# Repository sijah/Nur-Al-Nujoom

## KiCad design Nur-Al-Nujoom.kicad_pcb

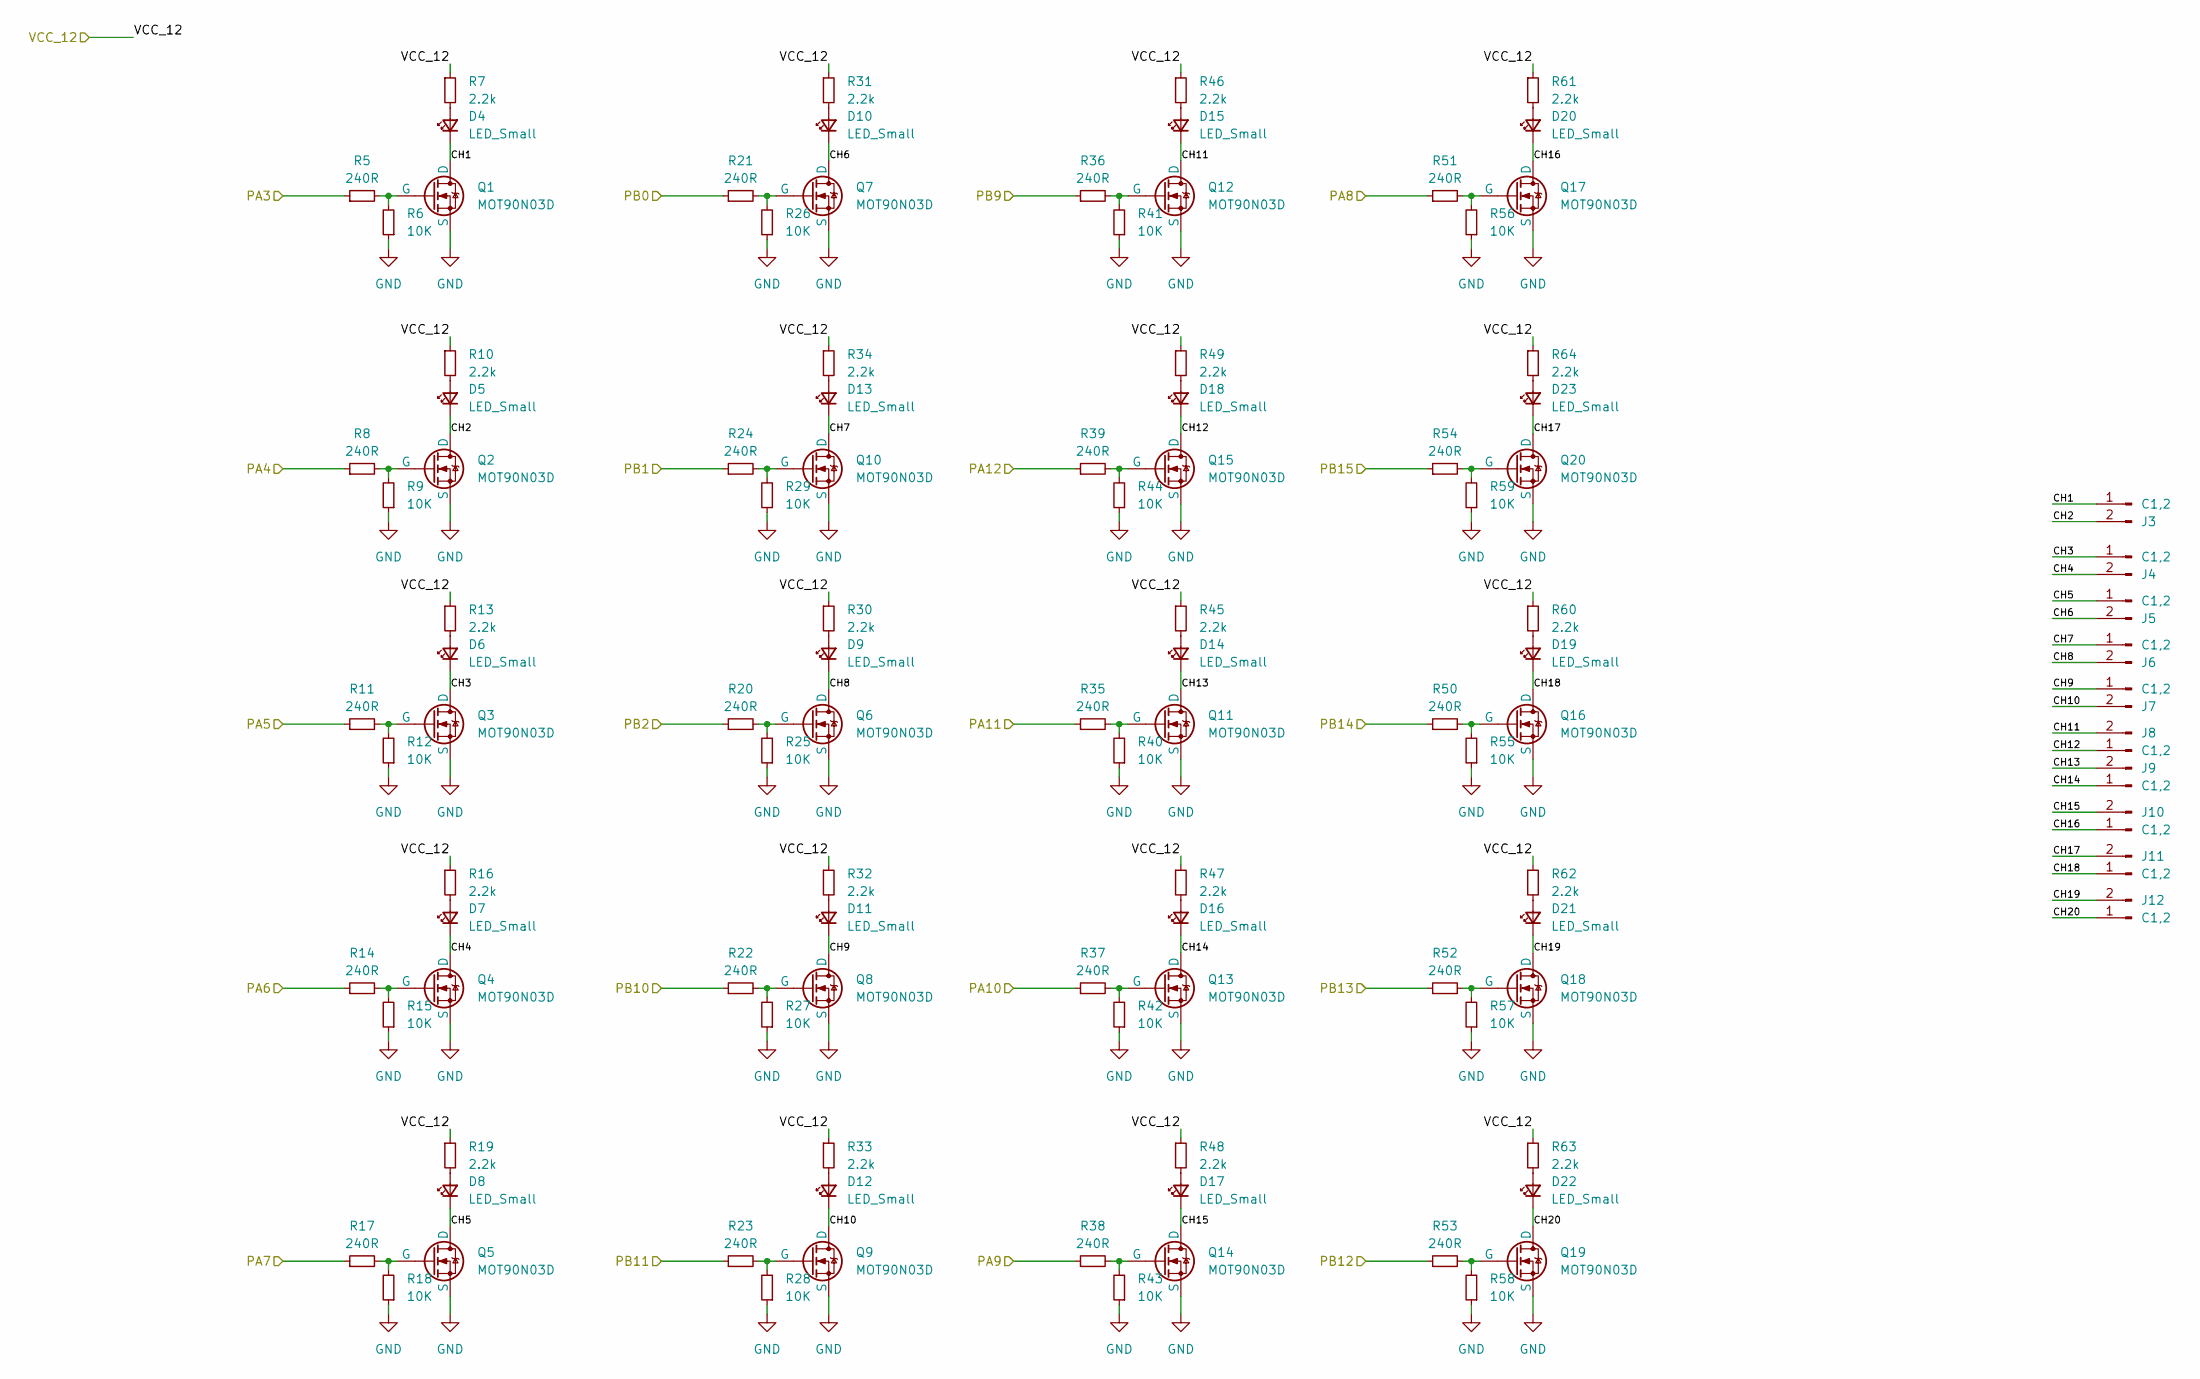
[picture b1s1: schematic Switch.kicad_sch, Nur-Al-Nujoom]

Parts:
D4, D5, D6, D7, D8, D9, D10, D11, D12, D13, D14, D15, D16, D17, D18, D19, D20, D21, D22, D23: LED_Small; LED_0603_1608Metric
J3, J4, J5, J6, J7, J8, J9, J10, J11, J12: C1,2; TerminalBlock_Phoenix_MKDS-3-2-5.08_1x02_P5.08mm_Horizontal
Q1, Q2, Q3, Q4, Q5, Q6, Q7, Q8, Q9, Q10, Q11, Q12, Q13, Q14, Q15, Q16, Q17, Q18, Q19, Q20: MOT90N03D; TO-252-2; mpn MOT90N03D
R5, R8, R11, R14, R17, R20, R21, R22, R23, R24, R35, R36, R37, R38, R39, R50, R51, R52, R53, R54: 240R; R_0603_1608Metric
R6, R9, R12, R15, R18, R25, R26, R27, R28, R29, R40, R41, R42, R43, R44, R55, R56, R57, R58, R59: 10K; R_0603_1608Metric
R7, R10, R13, R16, R19, R30, R31, R32, R33, R34, R45, R46, R47, R48, R49, R60, R61, R62, R63, R64: 2.2k; R_0603_1608Metric

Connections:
/12: R7.1, R10.1, R13.1, R16.1, R19.1, R30.1, R31.1, R32.1, R33.1, R34.1, R45.1, R46.1, R47.1, R48.1, R49.1, R60.1, R61.1, R62.1, R63.1, R64.1; also elsewhere on the board
/MCU/PA3: R5.1; also elsewhere on the board
/MCU/PA4: R8.1; also elsewhere on the board
/MCU/PA5: R11.1; also elsewhere on the board
/MCU/PA6: R14.1; also elsewhere on the board
/MCU/PA7: R17.1; also elsewhere on the board
/MCU/PA8: R51.1; also elsewhere on the board
/MCU/PA9: R38.1; also elsewhere on the board
/MCU/PA10: R37.1; also elsewhere on the board
/MCU/PA11: R35.1; also elsewhere on the board
/MCU/PA12: R39.1; also elsewhere on the board
/MCU/PB0: R21.1; also elsewhere on the board
/MCU/PB1: R24.1; also elsewhere on the board
/MCU/PB2: R20.1; also elsewhere on the board
/MCU/PB9: R36.1; also elsewhere on the board
/MCU/PB10: R22.1; also elsewhere on the board
/MCU/PB11: R23.1; also elsewhere on the board
/MCU/PB12: R53.1; also elsewhere on the board
/MCU/PB13: R52.1; also elsewhere on the board
/MCU/PB14: R50.1; also elsewhere on the board
/MCU/PB15: R54.1; also elsewhere on the board
/Switch/CH1: D4.1 (K), J3.1, Q1.2 (D)
/Switch/CH2: D5.1 (K), J3.2, Q2.2 (D)
/Switch/CH3: D6.1 (K), J4.1, Q3.2 (D)
/Switch/CH4: D7.1 (K), J4.2, Q4.2 (D)
/Switch/CH5: D8.1 (K), J5.1, Q5.2 (D)
/Switch/CH6: D10.1 (K), J5.2, Q7.2 (D)
/Switch/CH7: D13.1 (K), J6.1, Q10.2 (D)
/Switch/CH8: D9.1 (K), J6.2, Q6.2 (D)
/Switch/CH9: D11.1 (K), J7.1, Q8.2 (D)
/Switch/CH10: D12.1 (K), J7.2, Q9.2 (D)
/Switch/CH11: D15.1 (K), J8.2, Q12.2 (D)
/Switch/CH12: D18.1 (K), J8.1, Q15.2 (D)
/Switch/CH13: D14.1 (K), J9.2, Q11.2 (D)
/Switch/CH14: D16.1 (K), J9.1, Q13.2 (D)
/Switch/CH15: D17.1 (K), J10.2, Q14.2 (D)
/Switch/CH16: D20.1 (K), J10.1, Q17.2 (D)
/Switch/CH17: D23.1 (K), J11.2, Q20.2 (D)
/Switch/CH18: D19.1 (K), J11.1, Q16.2 (D)
/Switch/CH19: D21.1 (K), J12.2, Q18.2 (D)
/Switch/CH20: D22.1 (K), J12.1, Q19.2 (D)
GND: Q1.3 (S), Q2.3 (S), Q3.3 (S), Q4.3 (S), Q5.3 (S), Q6.3 (S), Q7.3 (S), Q8.3 (S), Q9.3 (S), Q10.3 (S), Q11.3 (S), Q12.3 (S), Q13.3 (S), Q14.3 (S), Q15.3 (S), Q16.3 (S), Q17.3 (S), Q18.3 (S), Q19.3 (S), Q20.3 (S), R6.1, R9.1, R12.1, R15.1, R18.1, R25.1, R26.1, R27.1, R28.1, R29.1, R40.1, R41.1, R42.1, R43.1, R44.1, R55.1, R56.1, R57.1, R58.1, R59.1; also elsewhere on the board
unnamed: D4.2 (A), R7.2
unnamed: D5.2 (A), R10.2
unnamed: D6.2 (A), R13.2
unnamed: D7.2 (A), R16.2
unnamed: D8.2 (A), R19.2
unnamed: D9.2 (A), R30.2
unnamed: D10.2 (A), R31.2
unnamed: D11.2 (A), R32.2
unnamed: D12.2 (A), R33.2
unnamed: D13.2 (A), R34.2
unnamed: D14.2 (A), R45.2
unnamed: D15.2 (A), R46.2
unnamed: D16.2 (A), R47.2
unnamed: D17.2 (A), R48.2
unnamed: D18.2 (A), R49.2
unnamed: D19.2 (A), R60.2
unnamed: D20.2 (A), R61.2
unnamed: D21.2 (A), R62.2
unnamed: D22.2 (A), R63.2
unnamed: D23.2 (A), R64.2
unnamed: Q1.1 (G), R5.2, R6.2
unnamed: Q2.1 (G), R8.2, R9.2
unnamed: Q3.1 (G), R11.2, R12.2
unnamed: Q4.1 (G), R14.2, R15.2
unnamed: Q5.1 (G), R17.2, R18.2
unnamed: Q6.1 (G), R20.2, R25.2
unnamed: Q7.1 (G), R21.2, R26.2
unnamed: Q8.1 (G), R22.2, R27.2
unnamed: Q9.1 (G), R23.2, R28.2
unnamed: Q10.1 (G), R24.2, R29.2
unnamed: Q11.1 (G), R35.2, R40.2
unnamed: Q12.1 (G), R36.2, R41.2
unnamed: Q13.1 (G), R37.2, R42.2
unnamed: Q14.1 (G), R38.2, R43.2
unnamed: Q15.1 (G), R39.2, R44.2
unnamed: Q16.1 (G), R50.2, R55.2
unnamed: Q17.1 (G), R51.2, R56.2
unnamed: Q18.1 (G), R52.2, R57.2
unnamed: Q19.1 (G), R53.2, R58.2
unnamed: Q20.1 (G), R54.2, R59.2

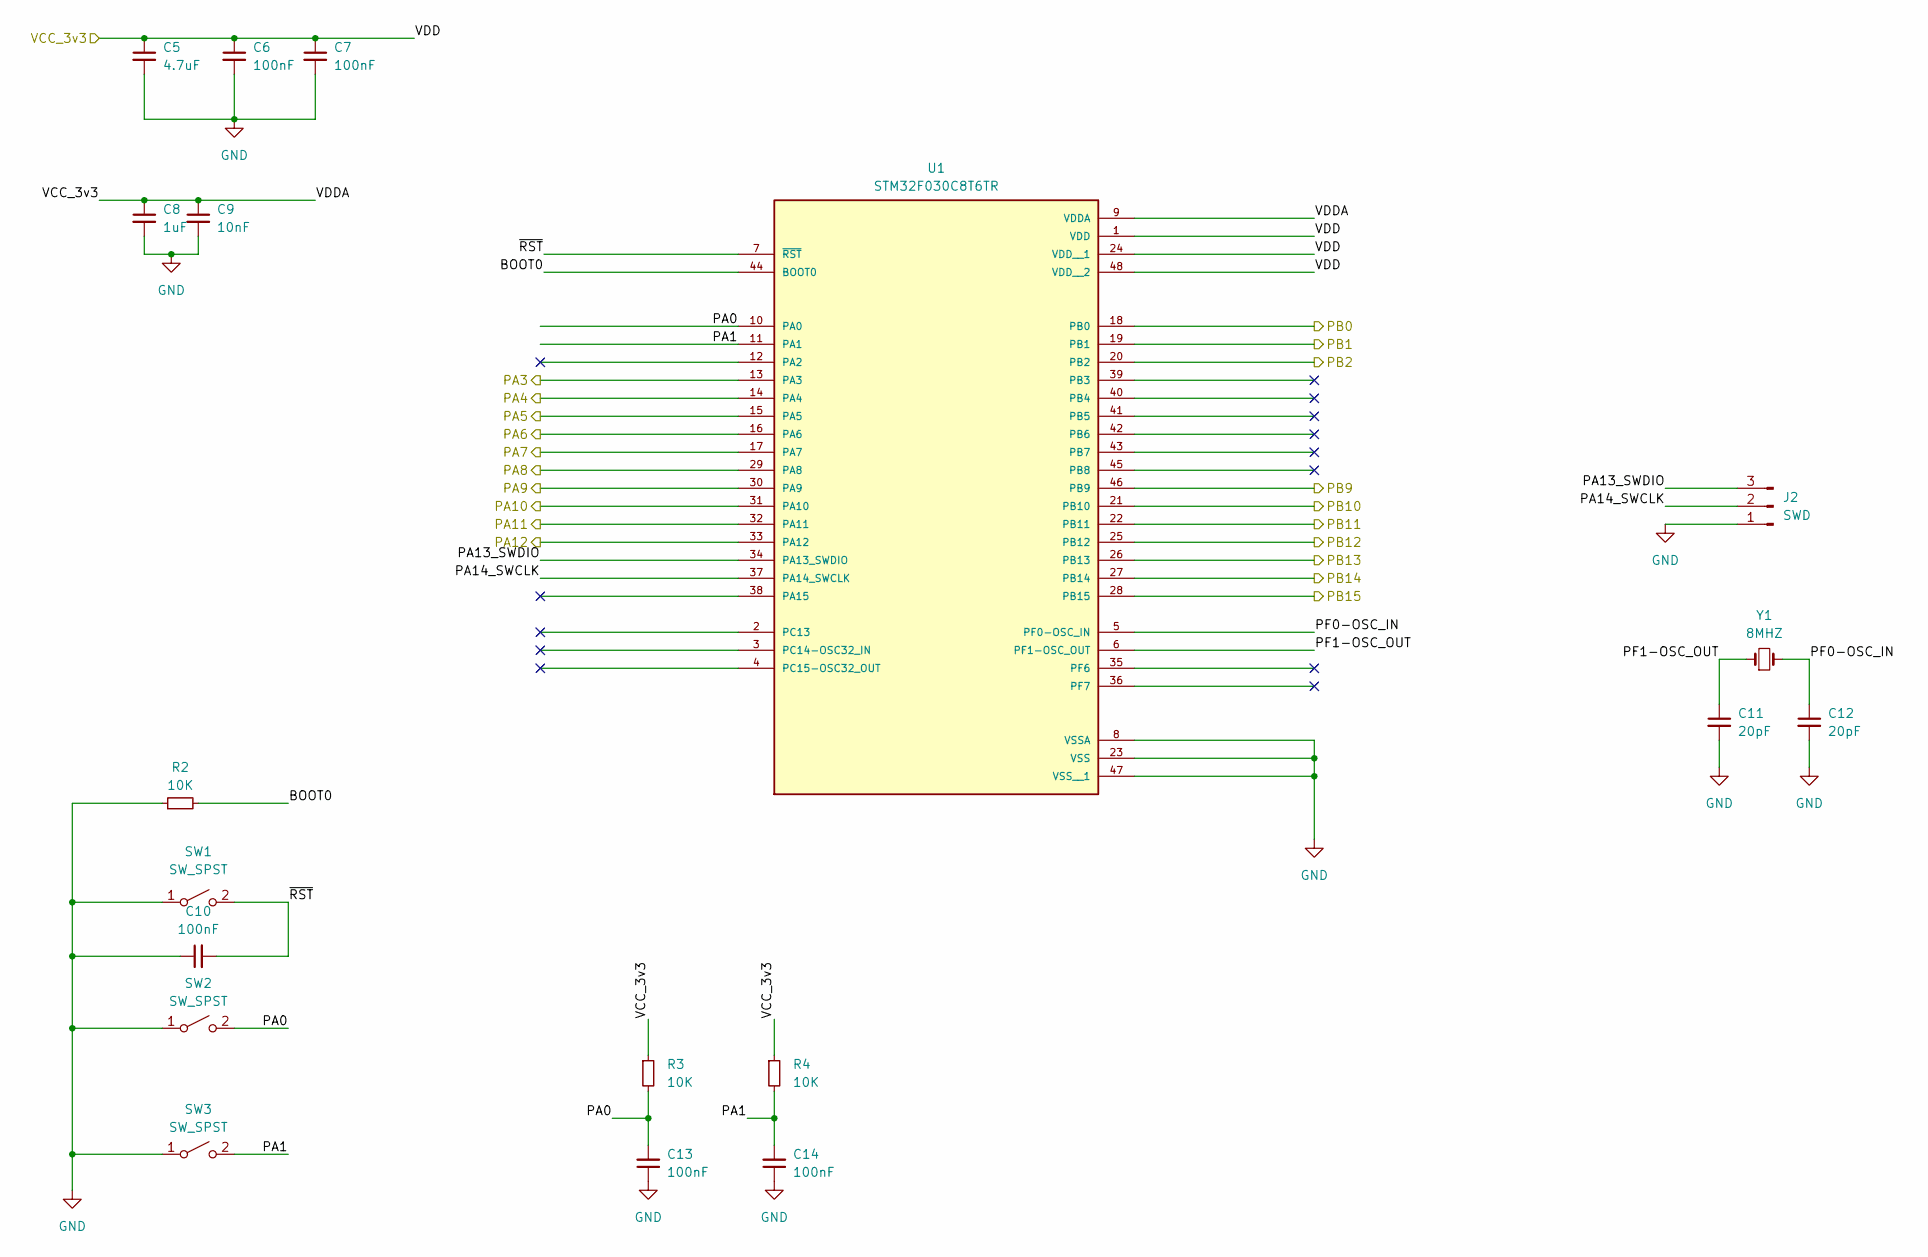
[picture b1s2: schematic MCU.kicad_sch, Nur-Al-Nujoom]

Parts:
C5: 4.7uF; C_0603_1608Metric
C6, C7, C10, C13, C14: 100nF; C_0603_1608Metric
C8: 1uF; C_0603_1608Metric
C9: 10nF; C_0603_1608Metric
C11, C12: 20pF; C_0603_1608Metric
J2: SWD; PinHeader_1x03_P2.54mm_Vertical
R2, R3, R4: 10K; R_0603_1608Metric
SW1, SW2, SW3: SW_SPST; SW_SPST_CK_RS282G05A3
U1: STM32F030C8T6TR; QFP50P900X900X160-48N; PARTREV 4
Y1: 8MHZ; Crystal_SMD_HC49-SD

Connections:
/MCU/BOOT0: R2.2, U1.44 (BOOT0)
/MCU/PA0: C13.2, R3.2, SW2.2 (B), U1.10 (PA0)
/MCU/PA1: C14.2, R4.2, SW3.2 (B), U1.11 (PA1)
/MCU/PA3: U1.13 (PA3); also elsewhere on the board
/MCU/PA4: U1.14 (PA4); also elsewhere on the board
/MCU/PA5: U1.15 (PA5); also elsewhere on the board
/MCU/PA6: U1.16 (PA6); also elsewhere on the board
/MCU/PA7: U1.17 (PA7); also elsewhere on the board
/MCU/PA8: U1.29 (PA8); also elsewhere on the board
/MCU/PA9: U1.30 (PA9); also elsewhere on the board
/MCU/PA10: U1.31 (PA10); also elsewhere on the board
/MCU/PA11: U1.32 (PA11); also elsewhere on the board
/MCU/PA12: U1.33 (PA12); also elsewhere on the board
/MCU/PA13_SWDIO: J2.3, U1.34 (PA13_SWDIO)
/MCU/PA14_SWCLK: J2.2, U1.37 (PA14_SWCLK)
/MCU/PB0: U1.18 (PB0); also elsewhere on the board
/MCU/PB1: U1.19 (PB1); also elsewhere on the board
/MCU/PB2: U1.20 (PB2); also elsewhere on the board
/MCU/PB9: U1.46 (PB9); also elsewhere on the board
/MCU/PB10: U1.21 (PB10); also elsewhere on the board
/MCU/PB11: U1.22 (PB11); also elsewhere on the board
/MCU/PB12: U1.25 (PB12); also elsewhere on the board
/MCU/PB13: U1.26 (PB13); also elsewhere on the board
/MCU/PB14: U1.27 (PB14); also elsewhere on the board
/MCU/PB15: U1.28 (PB15); also elsewhere on the board
/MCU/PF0-OSC_IN: C12.1, U1.5 (PF0-OSC_IN), Y1.2
/MCU/PF1-OSC_OUT: C11.1, U1.6 (PF1-OSC_OUT), Y1.1
/MCU/VCC_3v3: C5.1, C6.1, C7.1, C8.1, C9.1, R3.1, R4.1, U1.1 (VDD), U1.9 (VDDA), U1.24 (VDD__1), U1.48 (VDD__2); also elsewhere on the board
/MCU/~RST: C10.2, SW1.2 (B), U1.7 (~RST)
GND: C5.2, C6.2, C7.2, C8.2, C9.2, C10.1, C11.2, C12.2, C13.1, C14.1, J2.1, R2.1, SW1.1 (A), SW2.1 (A), SW3.1 (A), U1.8 (VSSA), U1.23 (VSS), U1.47 (VSS__1); also elsewhere on the board

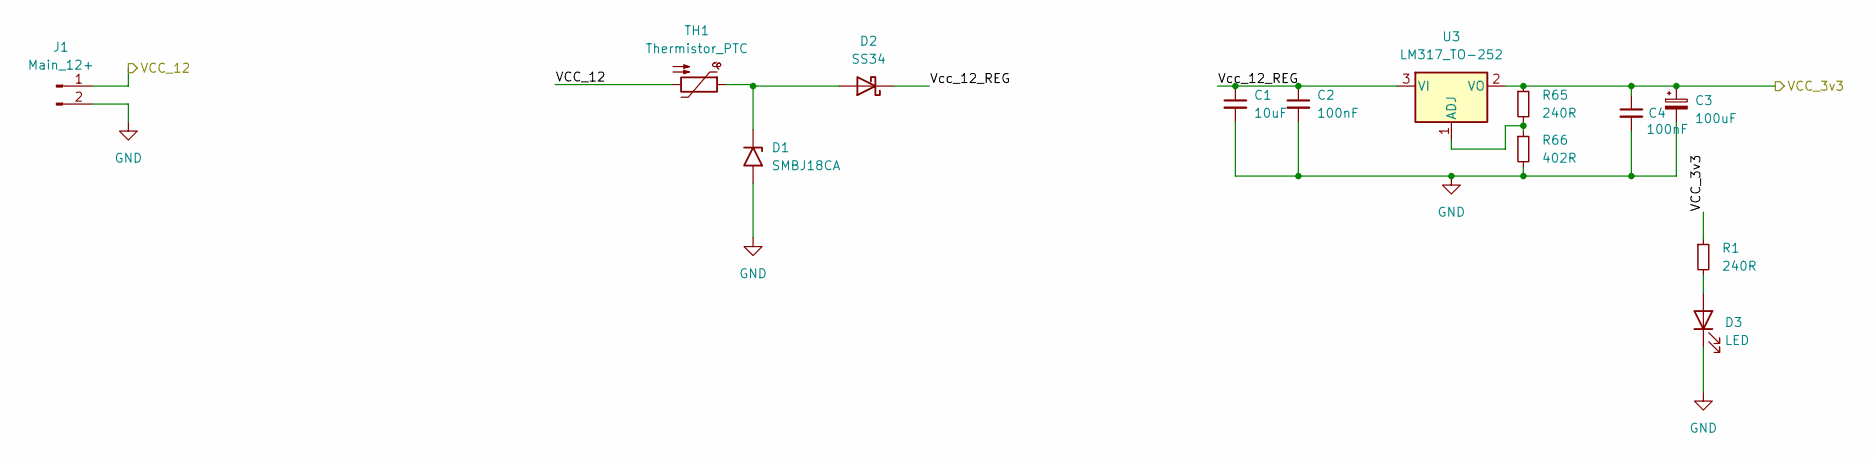
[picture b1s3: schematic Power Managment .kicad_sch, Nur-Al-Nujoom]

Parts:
C1: 10uF; C_0603_1608Metric
C2, C4: 100nF; C_0603_1608Metric
C3: 100uF; CP_Radial_D6.3mm_P2.50mm
D1: SMBJ18CA; D_SMB; mpn SMBJ18CA
D2: SS34; D_SMA
D3: LED; LED_0603_1608Metric
J1: Main_12+; TerminalBlock_Phoenix_MKDS-3-2-5.08_1x02_P5.08mm_Horizontal
R1, R65: 240R; R_0603_1608Metric
R66: 402R; R_0603_1608Metric
TH1: Thermistor_PTC; Fuse_1812_4532Metric
U3: LM317_TO-252; TO-252-2

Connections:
/12: J1.1, TH1.2; also elsewhere on the board
/MCU/VCC_3v3: C3.1, C4.1, R1.1, R65.1, U3.2 (VO); also elsewhere on the board
/Power Managment/Vcc_12_REG: C1.1, C2.1, D2.1 (K), U3.3 (VI)
GND: C1.2, C2.2, C3.2, C4.2, D1.2 (A2), D3.1 (K), J1.2, R66.2; also elsewhere on the board
unnamed: D1.1 (A1), D2.2 (A), TH1.1
unnamed: D3.2 (A), R1.2
unnamed: R65.2, R66.1, U3.1 (ADJ)

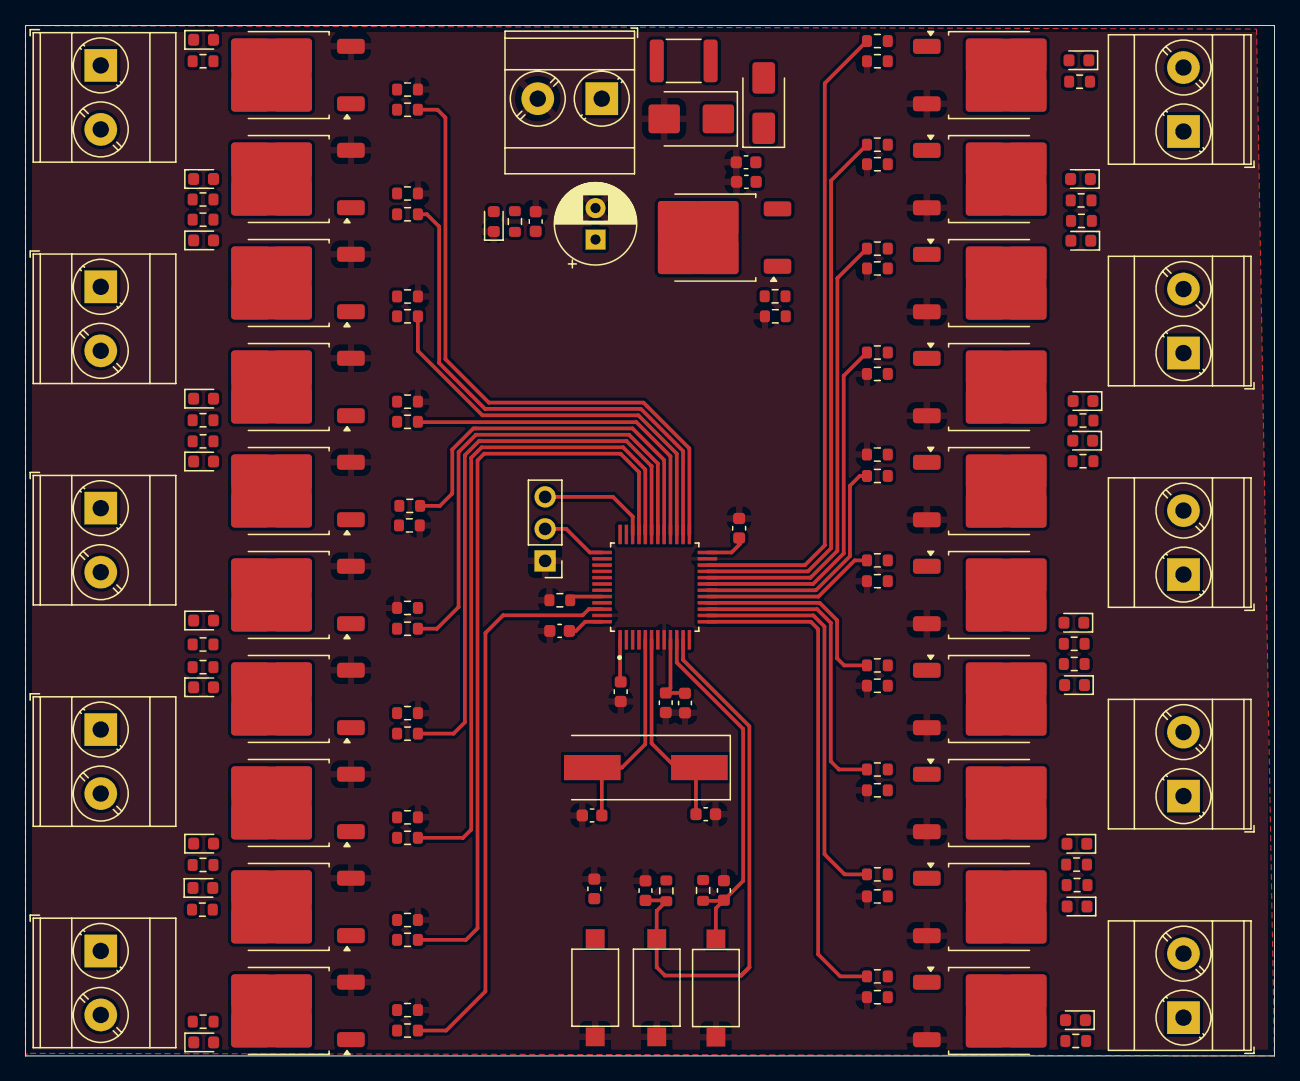
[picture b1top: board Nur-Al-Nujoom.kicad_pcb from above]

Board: 2 copper layers, 99.2 x 81.8 mm, 142 parts (0 on the bottom side), 95 nets.

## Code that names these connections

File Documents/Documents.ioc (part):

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Mcu.Name=STM32F030C8Tx
Mcu.Package=LQFP48
Mcu.UserName=STM32F030C8Tx
PA0.GPIOParameters=GPIO_PuPd
PA0.GPIO_PuPd=GPIO_PULLDOWN
PA0.Signal=GPIO_Output
PA1.Signal=GPIO_Output
PA10.Signal=GPIO_Output
PA11.Signal=GPIO_Input
PA12.Signal=GPIO_Input
PA13.Mode=Serial_Wire
PA13.Signal=SYS_SWDIO
PA14.Mode=Serial_Wire
PA14.Signal=SYS_SWCLK
PA2.Signal=GPIO_Output
PA3.Signal=GPIO_Output
PA4.Signal=GPIO_Output
PA5.Signal=GPIO_Output
PA6.Signal=GPIO_Output
PA7.Signal=GPIO_Output
PA8.Signal=GPIO_Output
PA9.Signal=GPIO_Output
PB0.Signal=GPIO_Output
PB1.Signal=GPIO_Output
PB10.Signal=GPIO_Output
PB11.Signal=GPIO_Output
PB12.Signal=GPIO_Output
PB13.Signal=GPIO_Output
PB14.Signal=GPIO_Output
PB15.Signal=GPIO_Output
PB2.Signal=GPIO_Output
PF0-OSC_IN.Mode=HSE-External-Oscillator
PF0-OSC_IN.Signal=RCC_OSC_IN
PF1-OSC_OUT.Mode=HSE-External-Oscillator
PF1-OSC_OUT.Signal=RCC_OSC_OUT
board=custom

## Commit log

2024-10-31 sch done open for review
2024-11-04 updated Routing
